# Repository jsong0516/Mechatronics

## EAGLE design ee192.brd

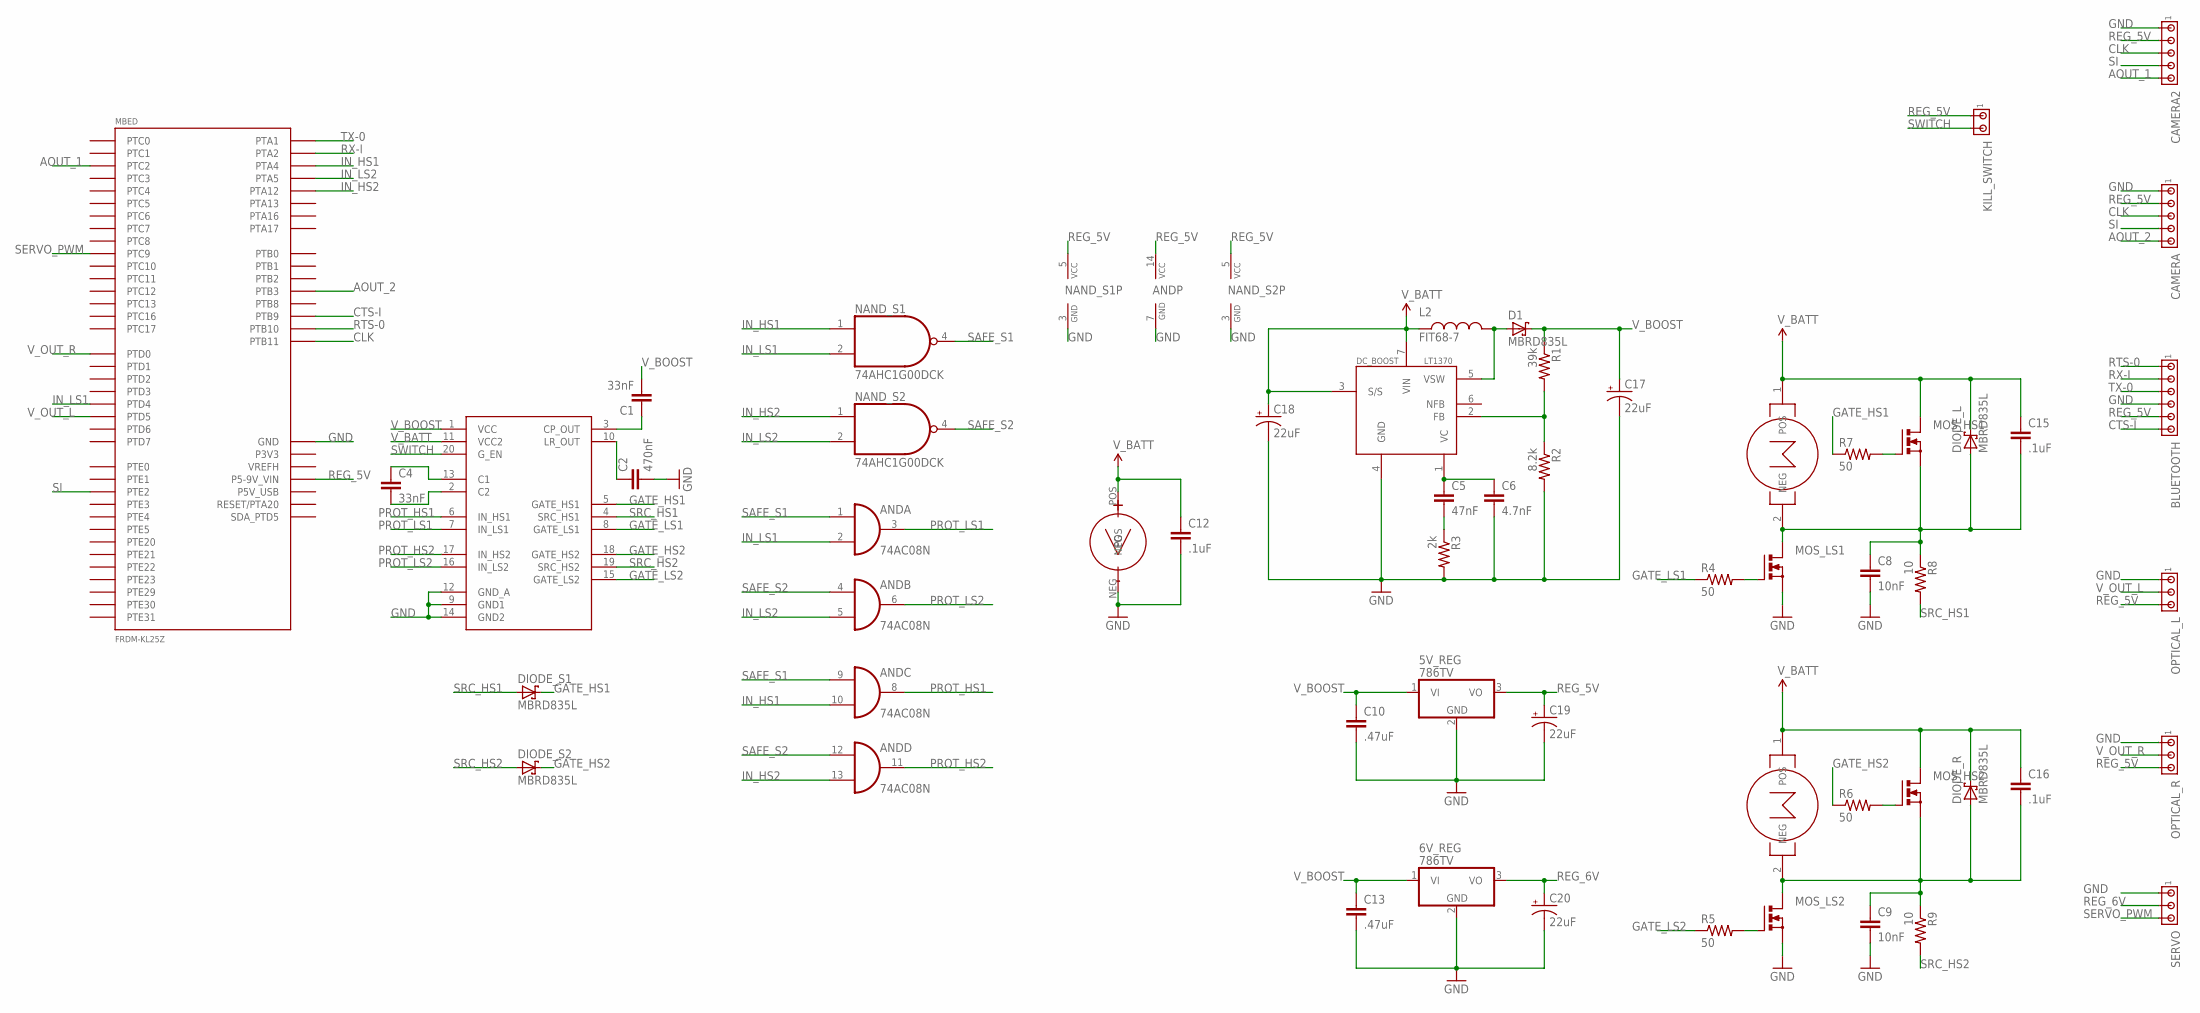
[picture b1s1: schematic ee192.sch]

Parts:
5V_REG, 6V_REG: 786TV; TO220V
AND: 74AC08N; DIL14
BATTERY: BATT
BLUETOOTH: MTA06-100; 10X06MTA
C1, C4: 33nF; 0805
C2: 470nF; 0805
C5: 47nF; 0805
C6: 4.7nF; 0805
C8, C9: 10nF; 0805
C10, C13: .47uF; 0805
C12, C15, C16: .1uF; 0805
C17, C18, C19, C20: 22uF; EIA7343
CAMERA, CAMERA2: MTA05-100; 10X05MTA
D1: MBRD835L; DPAK
DC_BOOST: LT1370; TO220-7
DIODE_L: MBRD835L; DPAK
DIODE_R: MBRD835L; DPAK
DIODE_S1, DIODE_S2: MBRD835L; DPAK
GATE_DRIVER: MC33883; SO20W
KILL_SWITCH: MTA02-100; 10X02MTA
L2: FIT68-7
MBED: FRDM-KL25Z
MOS_HS1, MOS_HS2: PMOSFET_NTO220BV; TO220BV
MOS_LS1, MOS_LS2: PMOSFET_NTO220BV; TO220BV
MOTOR_L: MOTOR
MOTOR_R: MOTOR
NAND_S1, NAND_S2: 74AHC1G00DCK; SC70-5
OPTICAL_L: MTA03-100; 10X03MTA
OPTICAL_R: MTA03-100; 10X03MTA
R1: 39k; 0805
R2: 8.2k; 0805
R3: 2k; 0805
R4, R5, R6, R7: 50; 0805
R8, R9: 10; 0805
SERVO: MTA03-100; 10X03MTA

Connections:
AOUT_1: CAMERA2.5, MBED.J10-10 (PTC2)
AOUT_2: CAMERA.5, MBED.J10-8 (PTB3)
CLK: CAMERA.3, CAMERA2.3, MBED.J9-7 (PTB11)
CTS-I: BLUETOOTH.1 (6), MBED.J9-3 (PTB9)
GATE_HS1: DIODE_S1.P$3 (C), GATE_DRIVER.5 (GATE_HS1), R7.1
GATE_HS2: DIODE_S2.P$3 (C), GATE_DRIVER.18 (GATE_HS2), R6.1
GATE_LS1: GATE_DRIVER.8 (GATE_LS1), R4.1
GATE_LS2: GATE_DRIVER.15 (GATE_LS2), R5.1
GND: 5V_REG.2 (GND), 6V_REG.2 (GND), AND.7 (GND), BATTERY.NEG, BLUETOOTH.3 (4), C2.2, C6.2, C8.2, C9.2, C10.2, C12.2, C13.2, C17.C (-), C18.C (-), C19.C (-), C20.C (-), CAMERA.1, CAMERA2.1, DC_BOOST.4 (GND), GATE_DRIVER.9 (GND1), GATE_DRIVER.12 (GND_A), GATE_DRIVER.14 (GND2), MBED.J2-14 (GND), MBED.J9-12 (GND), MBED.J9-14 (GND), MOS_LS1.S, MOS_LS2.S, NAND_S1.3 (GND), NAND_S2.3 (GND), OPTICAL_L.1, OPTICAL_R.1, R2.2, R3.2, SERVO.1
IN_HS1: AND.10 (I1), MBED.J1-10 (PTA4), NAND_S1.1 (I0)
IN_HS2: AND.13 (I1), MBED.J1-8 (PTA12), NAND_S2.1 (I0)
IN_LS1: AND.2 (I1), MBED.J1-6 (PTD4), NAND_S1.2 (I1)
IN_LS2: AND.5 (I1), MBED.J1-12 (PTA5), NAND_S2.2 (I1)
L_NEG_MOTOR: C8.1, C15.2, DIODE_L.P$1 (A), DIODE_L.P$2 (A), MOS_HS1.S, MOS_LS1.D, MOTOR_L.2 (NEG), R8.1
unnamed: C2.1, GATE_DRIVER.10 (LR_OUT)
unnamed: C1.1, GATE_DRIVER.3 (CP_OUT)
unnamed: C4.1, GATE_DRIVER.13 (C1)
unnamed: C4.2, GATE_DRIVER.2 (C2)
unnamed: DC_BOOST.2 (FB), R1.2, R2.1
unnamed: MOS_HS2.G, R6.2
unnamed: MOS_LS1.G, R4.2
unnamed: MOS_LS2.G, R5.2
unnamed: MOS_HS1.G, R7.2
unnamed: C5.2, R3.1
unnamed: C5.1, C6.1, DC_BOOST.1 (VC)
PROT_HS1: AND.8 (O), GATE_DRIVER.6 (IN_HS1)
PROT_HS2: AND.11 (O), GATE_DRIVER.17 (IN_HS2)
PROT_LS1: AND.3 (O), GATE_DRIVER.7 (IN_LS1)
PROT_LS2: AND.6 (O), GATE_DRIVER.16 (IN_LS2)
REG_5V: 5V_REG.3 (VO), AND.14 (VCC), BLUETOOTH.2 (5), C19.A (+), CAMERA.2, CAMERA2.2, KILL_SWITCH.1, MBED.J9-16 (P5-9V_VIN), NAND_S1.5 (VCC), NAND_S2.5 (VCC), OPTICAL_L.3, OPTICAL_R.3
REG_6V: 6V_REG.3 (VO), C20.A (+), SERVO.2
RTS-0: BLUETOOTH.6 (1), MBED.J9-5 (PTB10)
RX-I: BLUETOOTH.5 (2), MBED.J1-4 (PTA2)
R_NEG_MOTOR: C9.1, C16.2, DIODE_R.P$1 (A), DIODE_R.P$2 (A), MOS_HS2.S, MOS_LS2.D, MOTOR_R.2 (NEG), R9.1
SAFE_S1: AND.1 (I0), AND.9 (I0), NAND_S1.4 (O)
SAFE_S2: AND.4 (I0), AND.12 (I0), NAND_S2.4 (O)
SERVO_PWM: MBED.J1-16 (PTC9), SERVO.3
SI: CAMERA.4, CAMERA2.4, MBED.J9-9 (PTE2)
SRC_HS1: DIODE_S1.P$1 (A), DIODE_S1.P$2 (A), GATE_DRIVER.4 (SRC_HS1), R8.2
SRC_HS2: DIODE_S2.P$1 (A), DIODE_S2.P$2 (A), GATE_DRIVER.19 (SRC_HS2), R9.2
SWITCH: GATE_DRIVER.20 (G_EN), KILL_SWITCH.2
TX-0: BLUETOOTH.4 (3), MBED.J1-2 (PTA1)
VSW_LINE: D1.P$1 (A), D1.P$2 (A), DC_BOOST.5 (VSW), L2.P$2
V_BATT: BATTERY.POS, C12.1, C15.1, C16.1, C18.A (+), DC_BOOST.3 (S/S), DC_BOOST.7 (VIN), DIODE_L.P$3 (C), DIODE_R.P$3 (C), GATE_DRIVER.11 (VCC2), L2.P$1, MOS_HS1.D, MOS_HS2.D, MOTOR_L.1 (POS), MOTOR_R.1 (POS)
V_BOOST: 5V_REG.1 (VI), 6V_REG.1 (VI), C1.2, C10.1, C13.1, C17.A (+), D1.P$3 (C), GATE_DRIVER.1 (VCC), R1.1
V_OUT_L: MBED.J2-4 (PTD5), OPTICAL_L.2
V_OUT_R: MBED.J2-6 (PTD0), OPTICAL_R.2

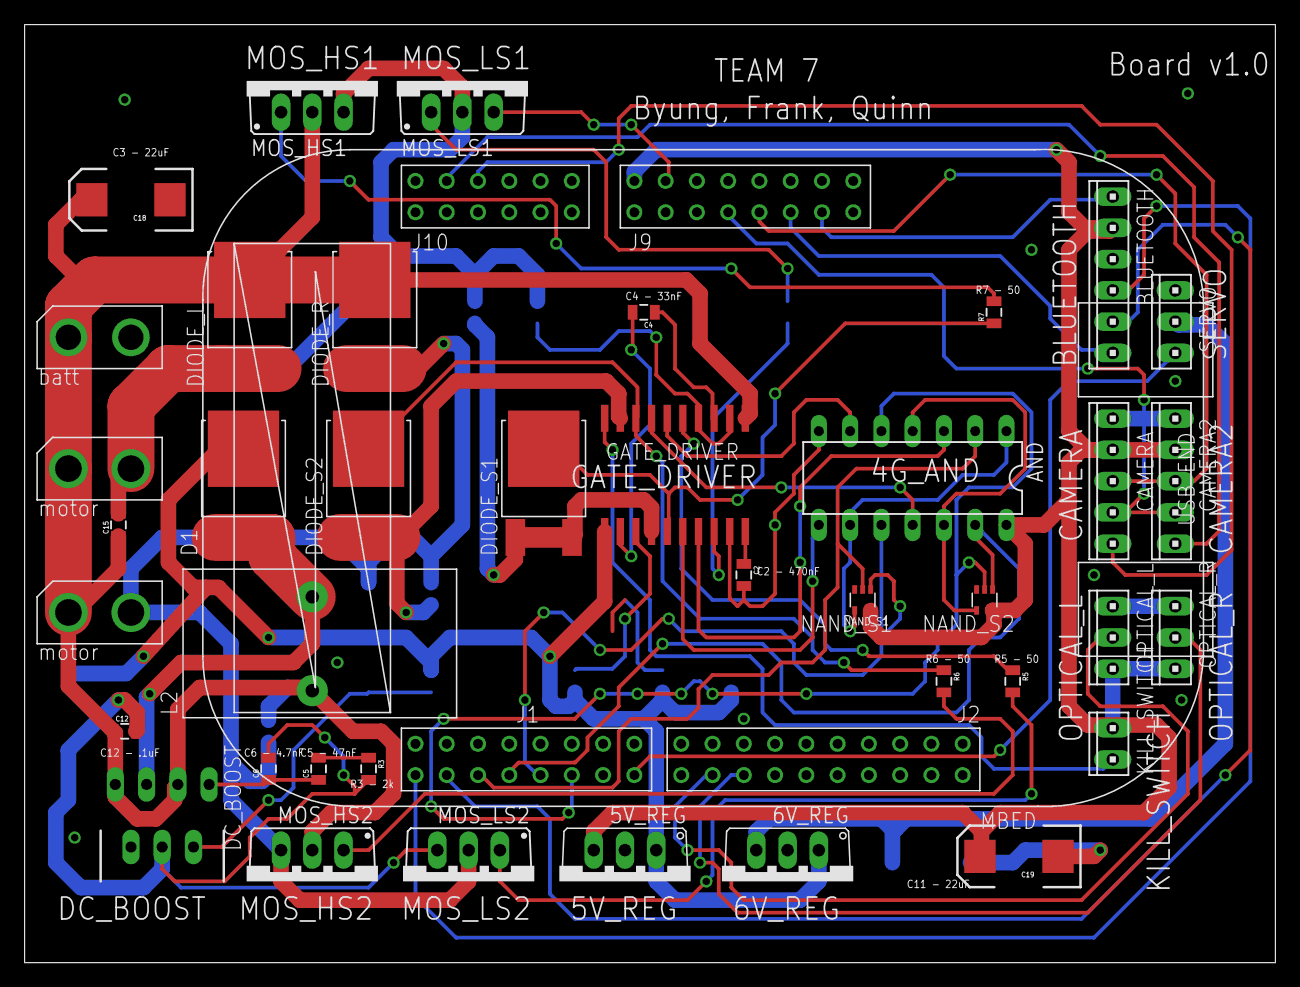
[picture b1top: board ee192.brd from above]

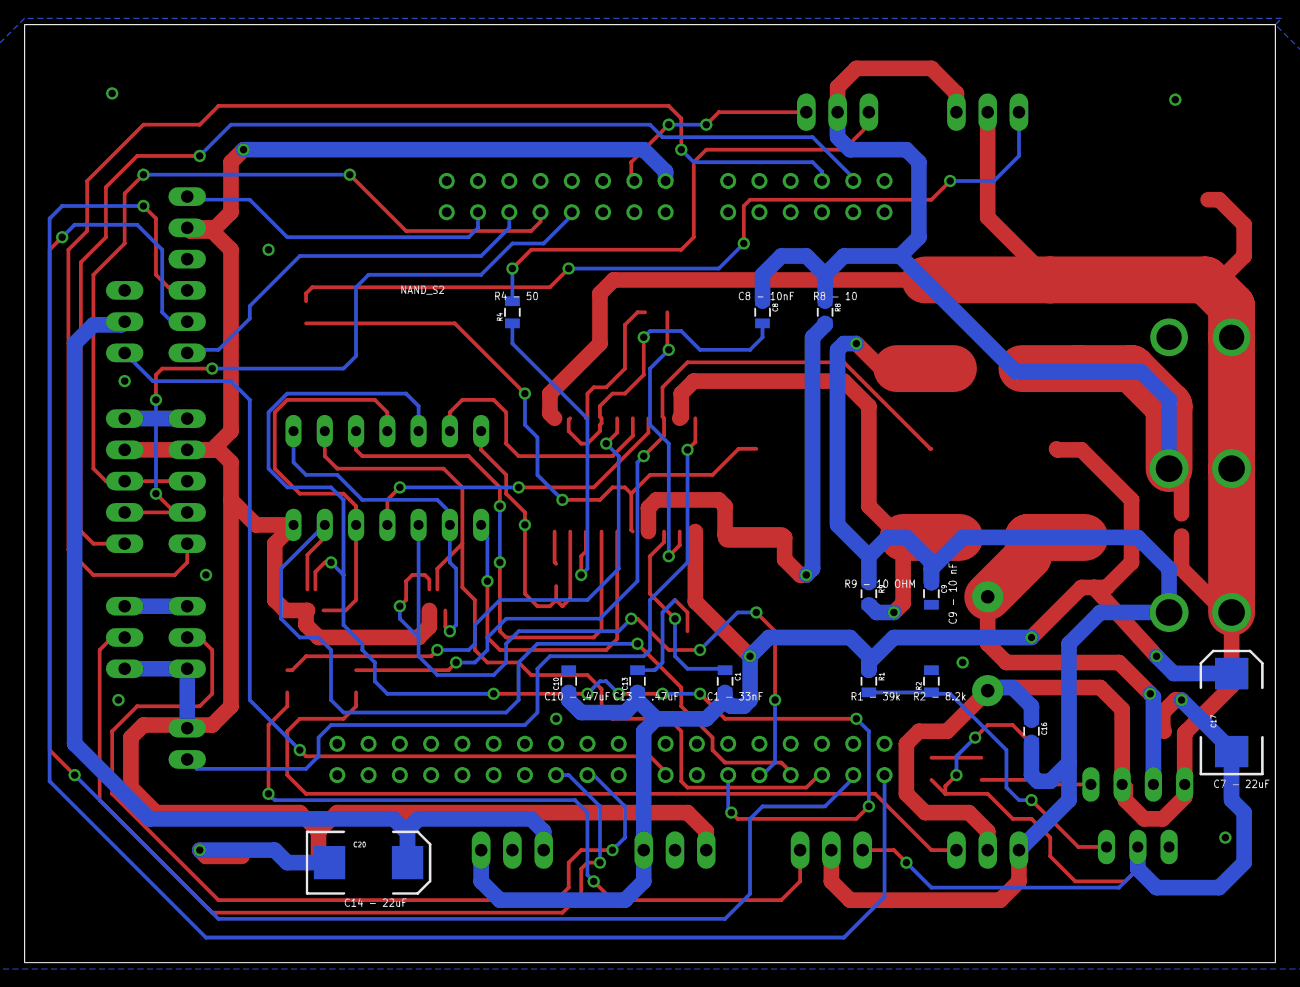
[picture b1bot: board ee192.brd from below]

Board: 2 copper layers, 101.6 x 76.2 mm, 53 parts (13 on the bottom side), 47 nets.

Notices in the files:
parts and their libraries:
SparkFun-Passives: Licensing: Creative Commons ShareAlike 4.0 International - https://creativecommons.org/licenses/by-sa/4.0
